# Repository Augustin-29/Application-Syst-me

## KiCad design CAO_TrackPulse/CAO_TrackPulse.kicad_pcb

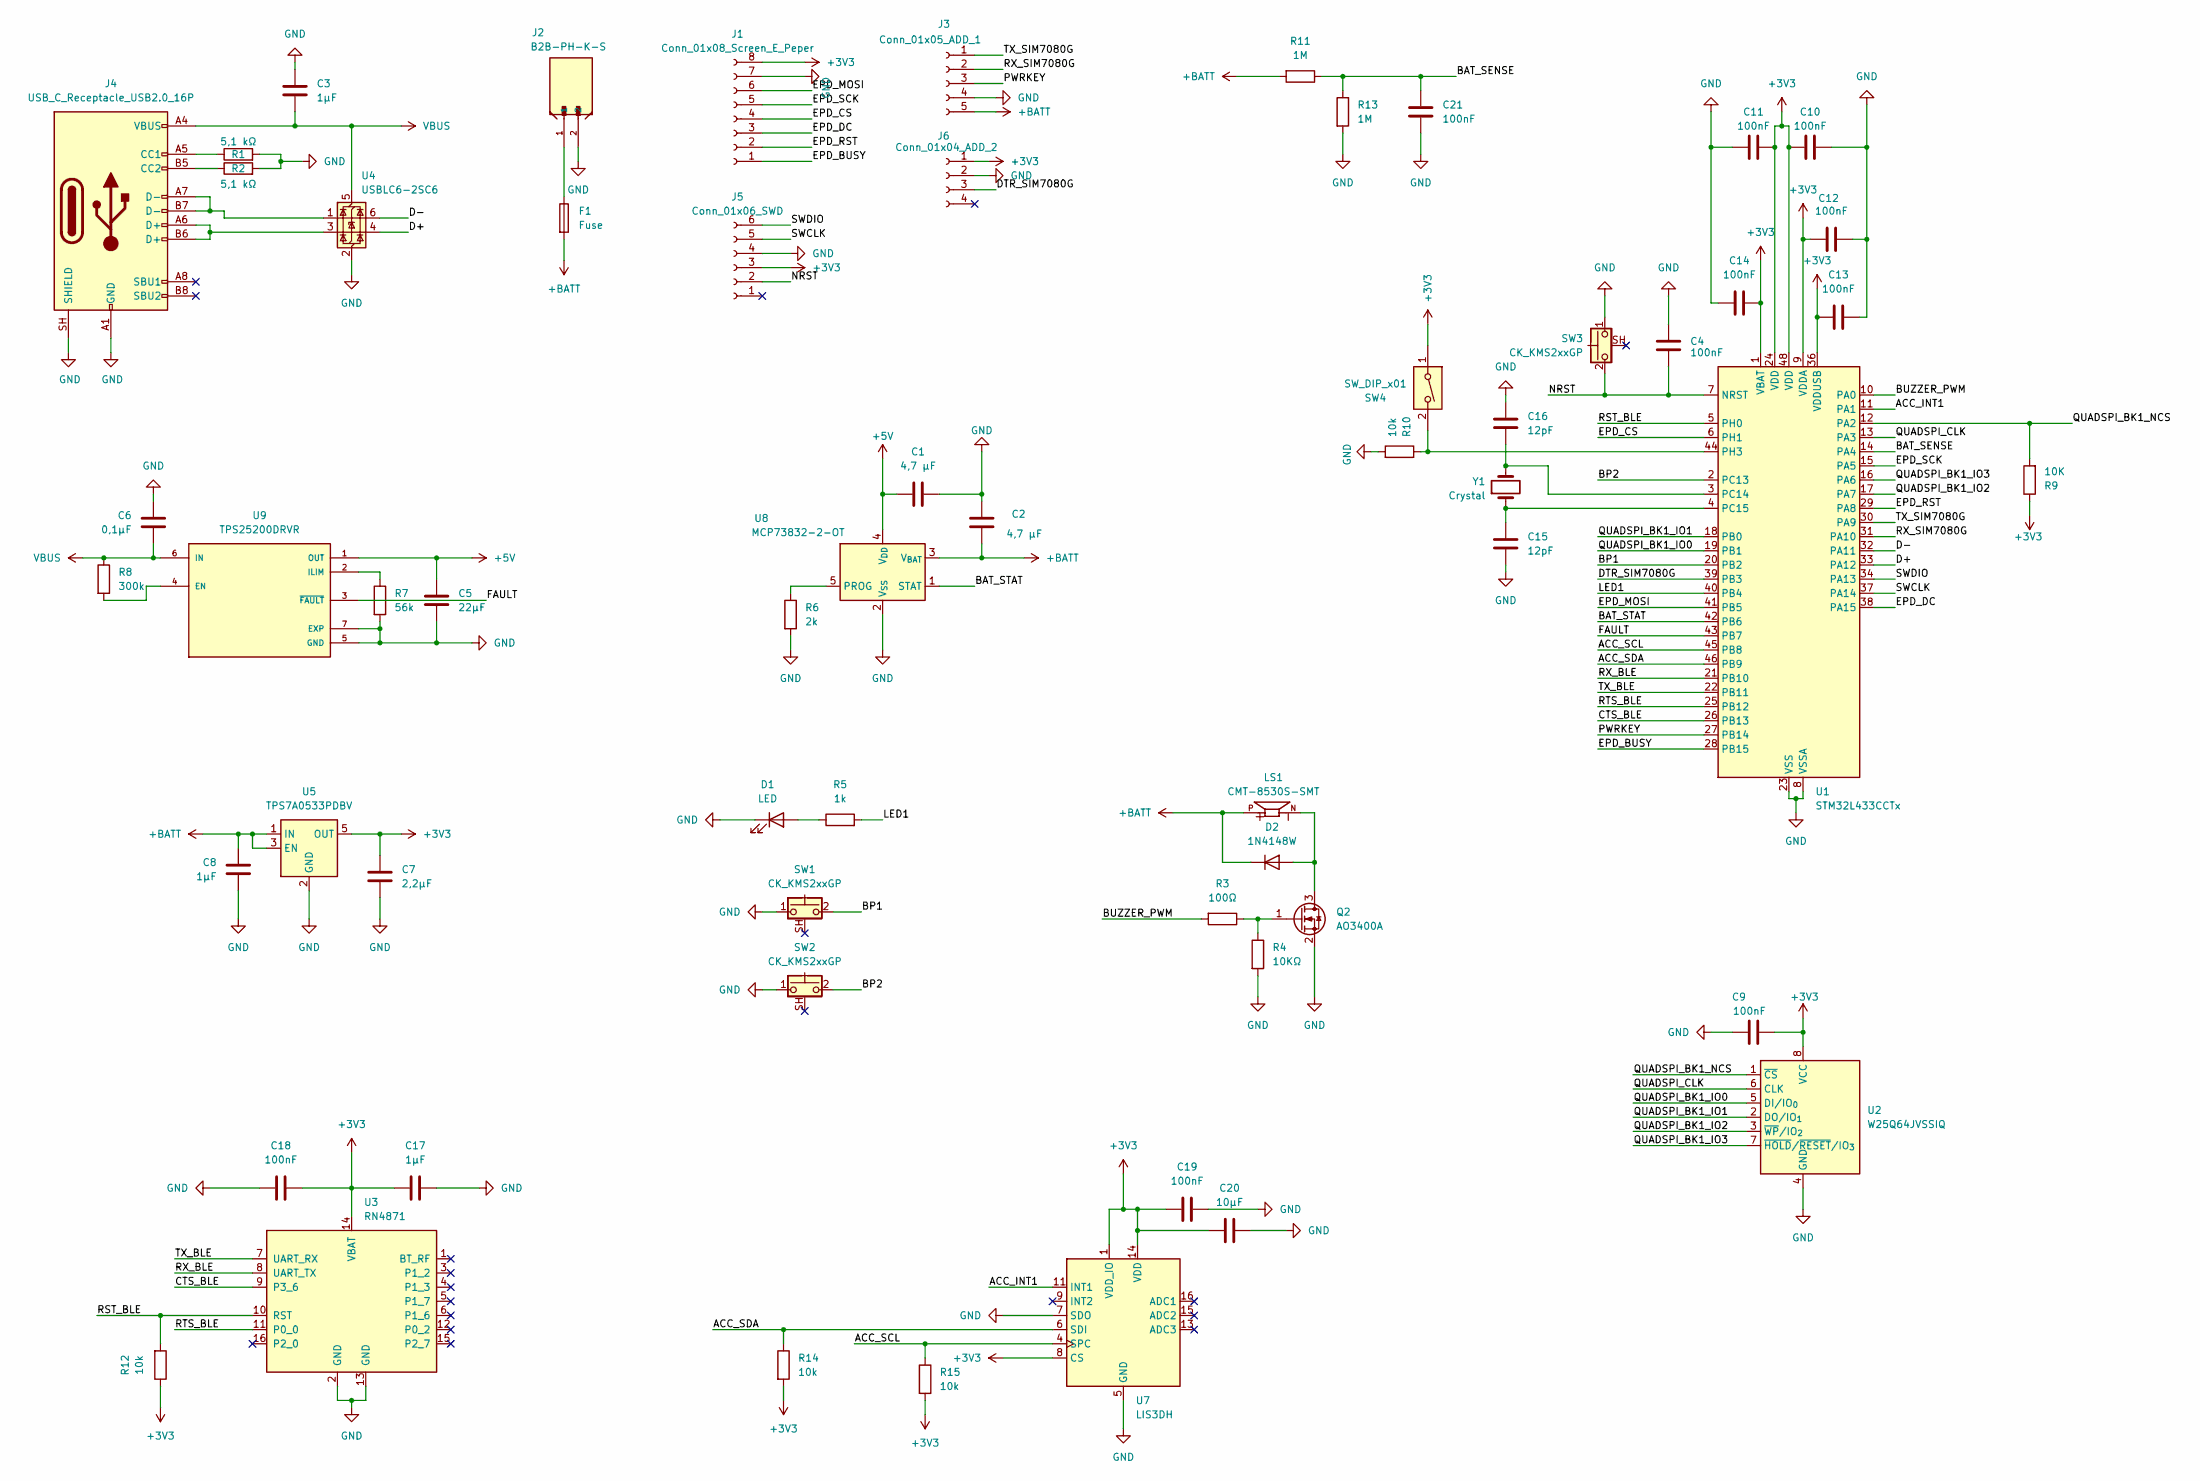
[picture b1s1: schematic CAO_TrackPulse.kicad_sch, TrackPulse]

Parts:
C1, C2: 4,7 µF; C_0805_2012Metric_Pad1.18x1.45mm_HandSolder
C3, C8, C17: 1µF; C_0805_2012Metric_Pad1.18x1.45mm_HandSolder
C4, C9, C10, C11, C12, C13, C14, C18, C19, C21: 100nF; C_0805_2012Metric_Pad1.18x1.45mm_HandSolder
C5: 22µF; C_0805_2012Metric_Pad1.18x1.45mm_HandSolder
C6: 0,1µF; C_0805_2012Metric_Pad1.18x1.45mm_HandSolder
C7: 2,2µF; C_0805_2012Metric_Pad1.18x1.45mm_HandSolder
C15, C16: 12pF; C_0805_2012Metric_Pad1.18x1.45mm_HandSolder
C20: 10µF; C_0805_2012Metric_Pad1.18x1.45mm_HandSolder
D1: LED; LED_0805_2012Metric_Pad1.15x1.40mm_HandSolder
D2: 1N4148W; D_SOD-123
F1: Fuse; Fuse_0805_2012Metric_Pad1.15x1.40mm_HandSolder
J1: Conn_01x08_Screen_E_Peper; PinHeader_1x08_P2.54mm_Vertical
J2: B2B-PH-K-S; JST_B2B-PH-K-S
J3: Conn_01x05_ADD_1; PinHeader_1x05_P2.54mm_Vertical
J4: USB_C_Receptacle_USB2.0_16P; USB_C_Receptacle_HRO_TYPE-C-31-M-12
J5: Conn_01x06_SWD; Tag-Connect_TC2030-IDC-NL_2x03_P1.27mm_Vertical
J6: Conn_01x04_ADD_2; PinHeader_1x04_P2.54mm_Vertical
LS1: CMT-8530S-SMT; MagneticBuzzer_CUI_CMT-8504
Q2: AO3400A; SOT-23
R1, R2: 5,1 kΩ; C_0805_2012Metric_Pad1.18x1.45mm_HandSolder
R3: 100Ω; C_0805_2012Metric_Pad1.18x1.45mm_HandSolder
R4: 10KΩ; C_0805_2012Metric_Pad1.18x1.45mm_HandSolder
R5: 1k; C_0805_2012Metric_Pad1.18x1.45mm_HandSolder
R6: 2k; C_0805_2012Metric_Pad1.18x1.45mm_HandSolder
R7: 56k; C_0805_2012Metric_Pad1.18x1.45mm_HandSolder
R8: 300k; C_0805_2012Metric_Pad1.18x1.45mm_HandSolder
R9: 10K; C_0805_2012Metric_Pad1.18x1.45mm_HandSolder
R10, R12, R14, R15: 10k; C_0805_2012Metric_Pad1.18x1.45mm_HandSolder
R11, R13: 1M; C_0805_2012Metric_Pad1.18x1.45mm_HandSolder
SW1, SW2, SW3: CK_KMS2xxGP; SW_SPST_CK_KMS2xxGP
SW4: SW_DIP_x01; SW_DIP_SPSTx01_Slide_Omron_A6S-110x_W8.9mm_P2.54mm
U1: STM32L433CCTx; LQFP-48_7x7mm_P0.5mm
U2: W25Q64JVSSIQ; SOIC-8_5.3x5.3mm_P1.27mm
U3: RN4871; Microchip_RN4871
U4: USBLC6-2SC6; SOT-23-6
U5: TPS7A0533PDBV; SOT-23-5
U7: LIS3DH; LGA-16_3x3mm_P0.5mm_LayoutBorder3x5y
U8: MCP73832-2-OT; SOT-23-5
U9: TPS25200DRVR; WSON-6-1EP_2x2mm_P0.65mm_EP1x1.6mm; PARTREV D
Y1: Crystal; Crystal_SMD_3215-2Pin_3.2x1.5mm

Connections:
+3V3: C7.1, C9.2, C10.1, C11.1, C12.1, C13.1, C14.2, C17.1, C18.2, C19.1, C20.1, J1.8, J5.3, J6.1, R9.1, R12.1, R14.2, R15.2, SW4.1, U1.1 (VBAT), U1.9 (VDDA), U1.24 (VDD), U1.36 (VDDUSB), U1.48 (VDD), U2.8 (VCC), U3.14 (VBAT), U5.5 (OUT), U7.1 (VDD_IO), U7.8 (CS), U7.14 (VDD)
+5V: C1.2, C5.1, U8.4 (V_{DD}), U9.1 (OUT)
+BATT: C2.1, C8.2, D2.1 (K), F1.2, J3.5, LS1.P, R11.2, U5.1 (IN), U5.3 (EN), U8.3 (V_{BAT})
/ACC_INT1: U1.11 (PA1), U7.11 (INT1)
/ACC_SCL: R15.1, U1.45 (PB8), U7.4 (SPC)
/ACC_SDA: R14.1, U1.46 (PB9), U7.6 (SDI)
/BAT_SENSE: C21.1, R11.1, R13.1, U1.14 (PA4)
/BAT_STAT: U1.42 (PB6), U8.1 (STAT)
/BP1: SW1.2, U1.20 (PB2)
/BP2: SW2.2, U1.2 (PC13)
/BUZZER_PWM: R3.2, U1.10 (PA0)
/CTS_BLE: U1.26 (PB13), U3.9 (P3_6)
/D+: U1.33 (PA12), U4.4 (I/O2)
/D-: U1.32 (PA11), U4.6 (I/O1)
/DTR_SIM7080G: J6.3, U1.39 (PB3)
/EPD_BUSY: J1.1, U1.28 (PB15)
/EPD_CS: J1.4, U1.6 (PH1)
/EPD_DC: J1.3, U1.38 (PA15)
/EPD_MOSI: J1.6, U1.41 (PB5)
/EPD_RST: J1.2, U1.29 (PA8)
/EPD_SCK: J1.5, U1.15 (PA5)
/FAULT: U1.43 (PB7), U9.3 (~FAULT)
/LED1: R5.2, U1.40 (PB4)
/NRST: C4.2, J5.2, SW3.2, U1.7 (NRST)
/PWRKEY: J3.3, U1.27 (PB14)
/QUADSPI_BK1_IO0: U1.19 (PB1), U2.5 (DI/IO_{0})
/QUADSPI_BK1_IO1: U1.18 (PB0), U2.2 (DO/IO_{1})
/QUADSPI_BK1_IO2: U1.17 (PA7), U2.3 (~WP/IO_{2})
/QUADSPI_BK1_IO3: U1.16 (PA6), U2.7 (~HOLD/~RESET/IO_{3})
/QUADSPI_BK1_NCS: R9.2, U1.12 (PA2), U2.1 (~CS)
/QUADSPI_CLK: U1.13 (PA3), U2.6 (CLK)
/RST_BLE: R12.2, U1.5 (PH0), U3.10 (RST)
/RTS_BLE: U1.25 (PB12), U3.11 (P0_0)
/RX_BLE: U1.21 (PB10), U3.8 (UART_TX)
/RX_SIM7080G: J3.2, U1.31 (PA10)
/SWCLK: J5.5, U1.37 (PA14)
/SWDIO: J5.6, U1.34 (PA13)
/TX_BLE: U1.22 (PB11), U3.7 (UART_RX)
/TX_SIM7080G: J3.1, U1.30 (PA9)
GND: C1.1, C2.2, C3.1, C4.1, C5.2, C6.1, C7.2, C8.1, C9.1, C10.2, C11.2, C12.2, C13.2, C14.1, C15.2, C16.1, C17.2, C18.1, C19.2, C20.2, C21.2, D1.1 (K), J1.7, J2.2, J3.4, J4.A1 (GND), J4.A12 (GND), J4.B1 (GND), J4.B12 (GND), J4.SH (SHIELD), J5.4, J6.2, Q2.2 (S), R1.2, R2.2, R4.2, R6.2, R7.2, R10.2, R13.2, SW1.1, SW2.1, SW3.1, U1.8 (VSSA), U1.23 (VSS), U1.35 (VSS), U1.47 (VSS), U2.4 (GND), U3.2 (GND), U3.13 (GND), U4.2 (GND), U5.2 (GND), U7.5 (GND), U7.7 (SDO), U7.10 (GND), U7.12 (GND), U8.2 (V_{SS}), U9.5 (GND), U9.7 (EXP)
unnamed: D1.2 (A), R5.1
unnamed: D2.2 (A), LS1.N, Q2.3 (D)
unnamed: F1.1, J2.1
unnamed: J4.A5 (CC1), R1.1
unnamed: J4.B5 (CC2), R2.1
unnamed: J4.A6 (D+), J4.B6 (D+), U4.3 (I/O2)
unnamed: J4.A7 (D-), J4.B7 (D-), U4.1 (I/O1)
unnamed: Q2.1 (G), R3.1, R4.1
unnamed: C16.2, U1.3 (PC14), Y1.2
unnamed: C15.1, U1.4 (PC15), Y1.1
unnamed: R10.1, SW4.2, U1.44 (PH3)
unnamed: R6.1, U8.5 (PROG)
unnamed: R8.2, U9.4 (EN)
unnamed: R7.1, U9.2 (ILIM)
VBUS: C3.2, C6.2, J4.A4 (VBUS), J4.A9 (VBUS), J4.B4 (VBUS), J4.B9 (VBUS), R8.1, U4.5 (VBUS), U9.6 (IN)

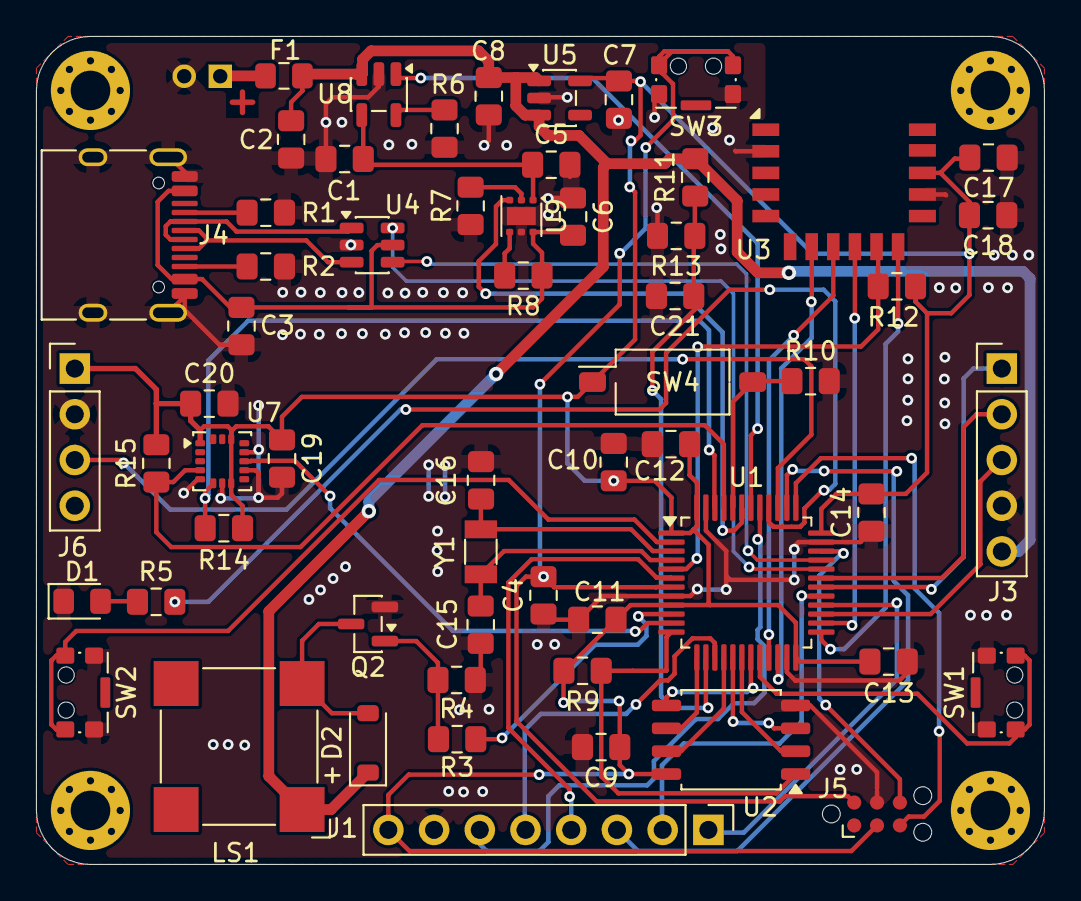
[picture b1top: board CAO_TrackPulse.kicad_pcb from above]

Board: 2 copper layers, 56.0 x 46.0 mm, 60 parts (1 on the bottom side), 55 nets.
